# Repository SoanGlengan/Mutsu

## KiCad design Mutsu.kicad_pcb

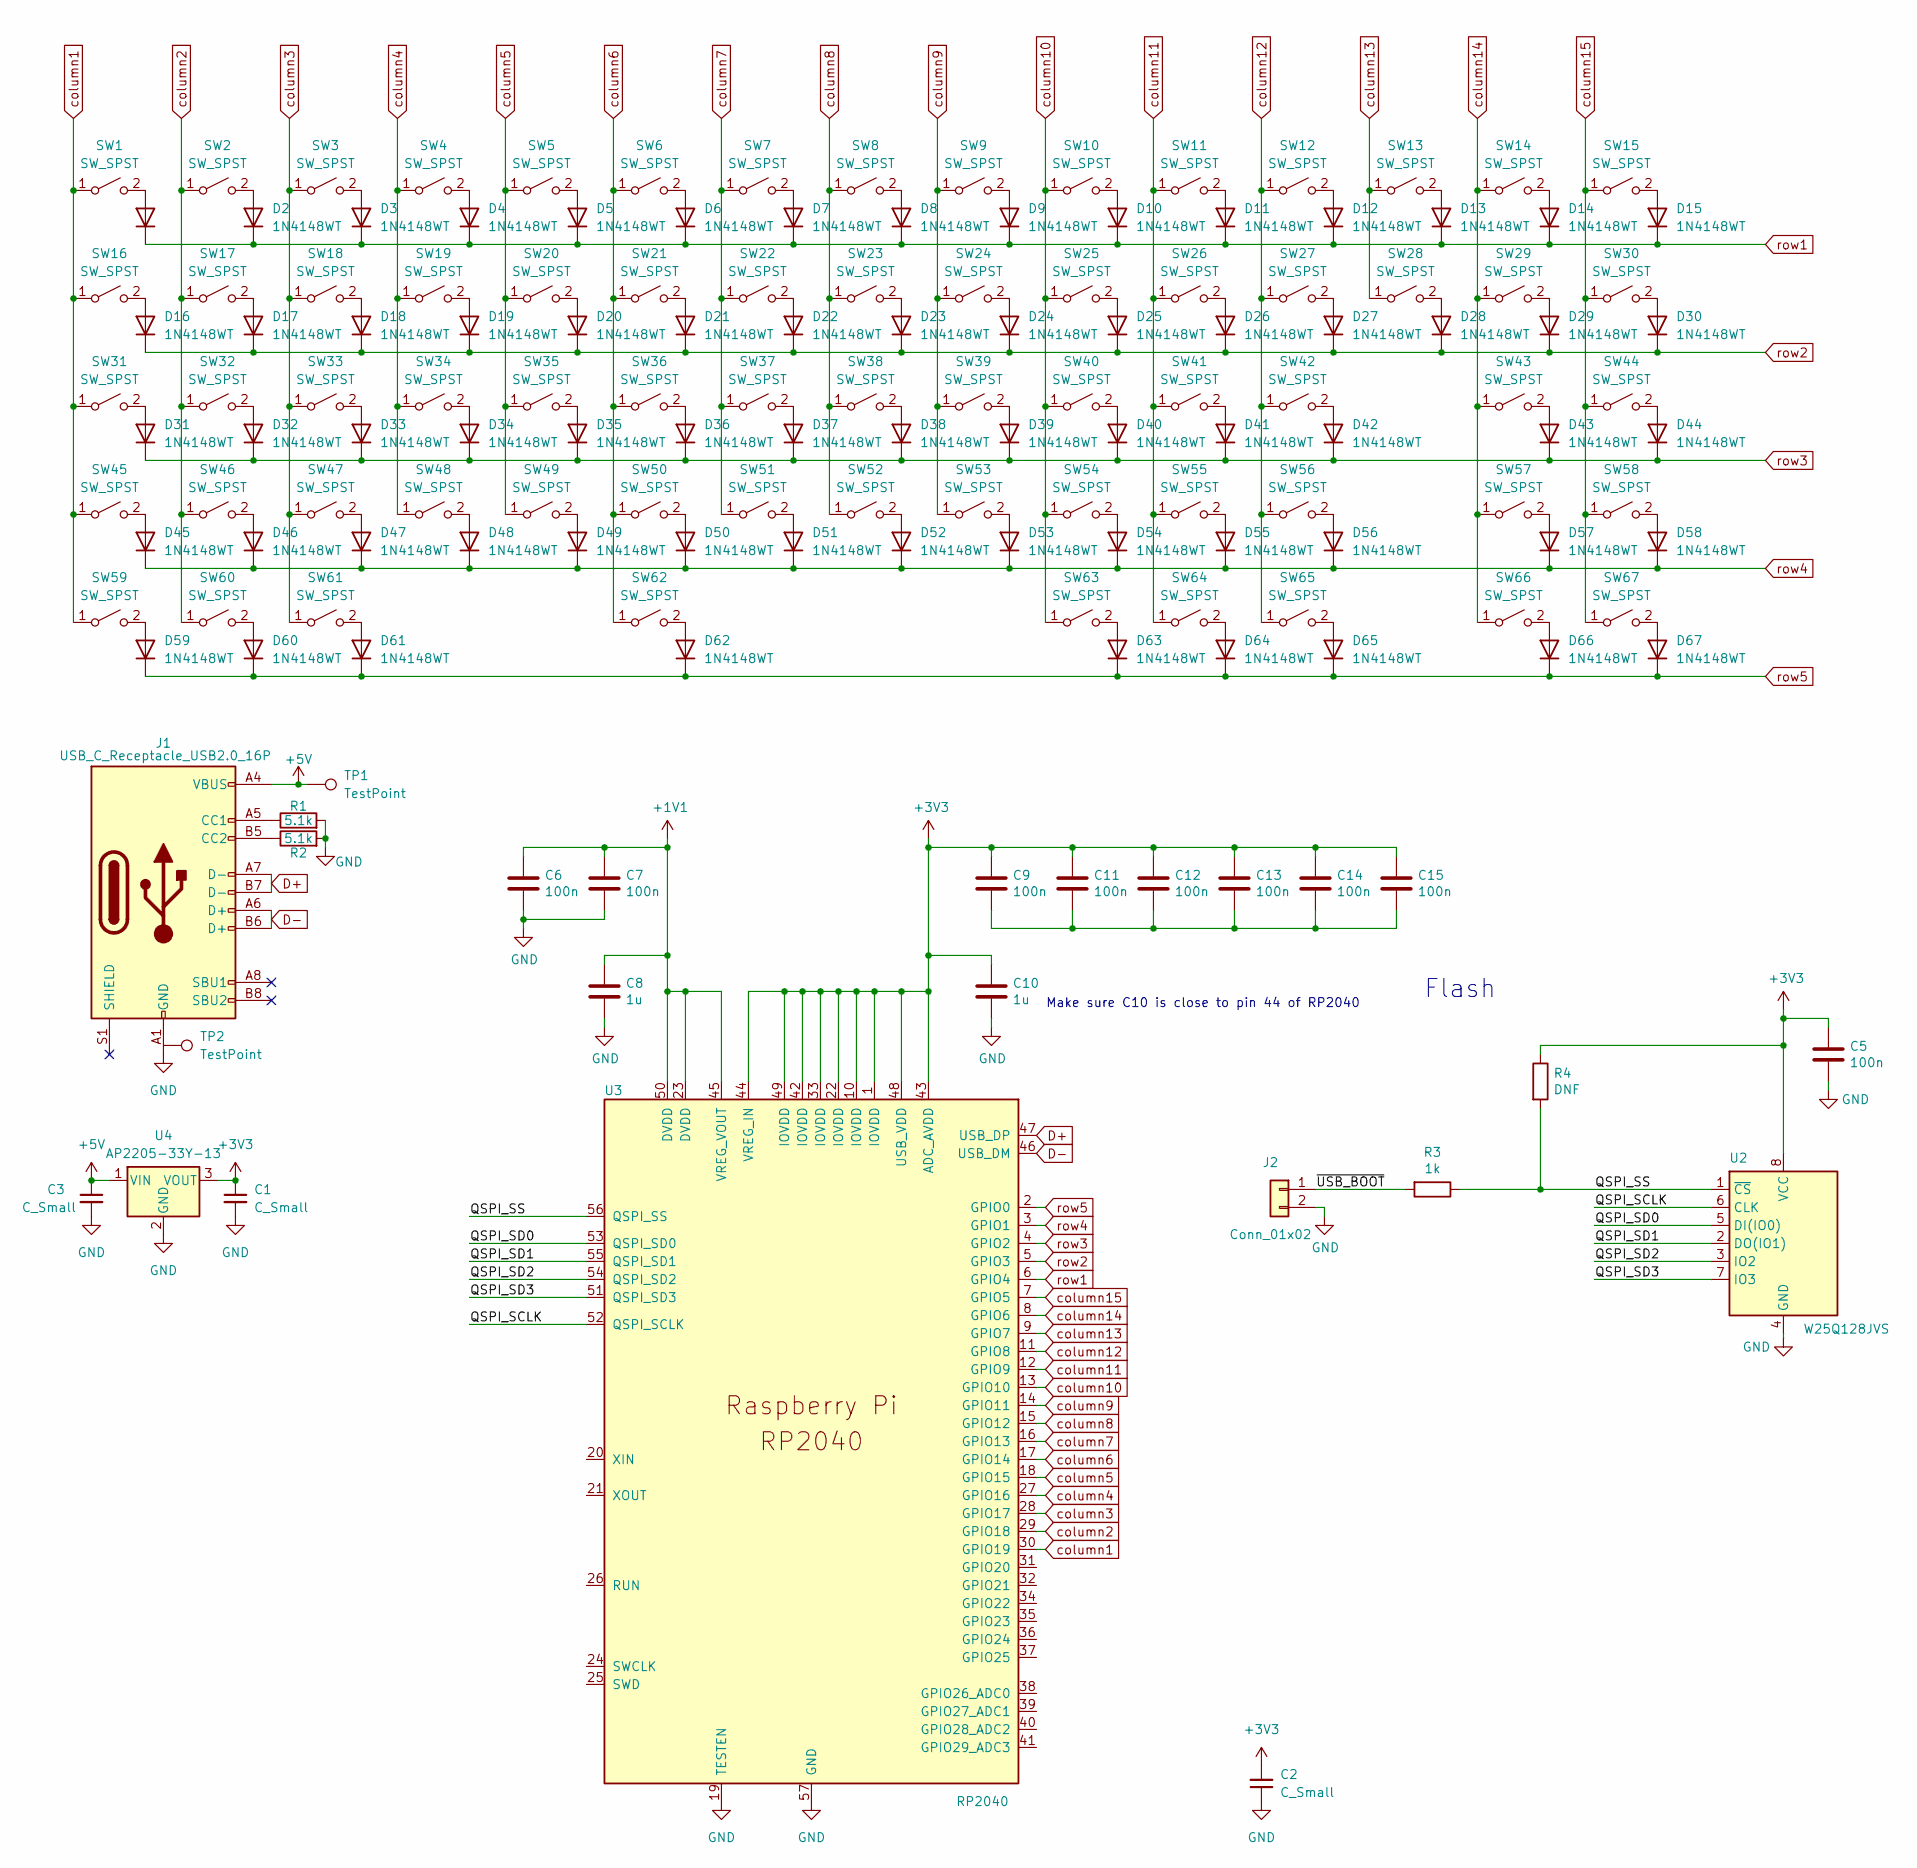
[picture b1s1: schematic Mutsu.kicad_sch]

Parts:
C1, C2, C3: C_Small
C5, C6, C7, C9, C11, C12, C13, C14, C15: 100n; C_0402_1005Metric
C8, C10: 1u; C_0402_1005Metric
D1: 1N4148wt; D_SOD-523
D2, D3, D4, D5, D6, D7, D8, D9, D10, D11, D12, D13, D14, D15, D16, D17, D18, D19, D20, D21, D22, D23, D24, D25, D26, D27, D28, D29, D30, D31, D32, D33, D34, D35, D36, D37, D38, D39, D40, D41, D42, D43, D44, D45, D46, D47, D48, D49, D50, D51, D52, D53, D54, D55, D56, D57, D58, D59, D60, D61, D62, D63, D64, D65, D66, D67: 1N4148WT; D_SOD-523
J1: USB_C_Receptacle_USB2.0_16P; USB_C_Receptacle_GCT_USB4105-xx-A_16P_TopMnt_Horizontal
J2: Conn_01x02; PinHeader_1x02_P2.54mm_Vertical
R1, R2: 5.1k
R3: 1k; R_0402_1005Metric
R4: DNF; R_0402_1005Metric
SW1, SW2, SW3, SW4, SW5, SW6, SW7, SW8, SW9, SW10, SW11, SW12, SW13, SW14, SW15, SW16, SW17, SW18, SW19, SW20, SW21, SW22, SW23, SW24, SW25, SW26, SW27, SW28, SW29, SW30, SW31, SW32, SW33, SW34, SW35, SW36, SW37, SW38, SW39, SW40, SW41, SW42, SW43, SW44, SW45, SW46, SW47, SW48, SW49, SW50, SW51, SW52, SW53, SW54, SW55, SW56, SW57, SW58, SW59, SW60, SW61, SW62, SW63, SW64, SW65, SW66, SW67: SW_SPST; Kailh_socket_PG1350
TP1, TP2: TestPoint
U2: W25Q128JVS; SOIC-8_5.23x5.23mm_P1.27mm
U3: RP2040; RP2040-QFN-56
U4: AP2205-33Y-13; SOT-89-3

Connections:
+1V1: C6.1, C7.1, C8.1, U3.23 (DVDD), U3.45 (VREG_VOUT), U3.50 (DVDD); also elsewhere on the board
+3V3: C1.1, C2.2, C5.1, C9.1, C10.1, C11.1, C12.1, C13.1, C14.1, C15.1, R4.1, U2.8 (VCC), U3.1 (IOVDD), U3.10 (IOVDD), U3.22 (IOVDD), U3.33 (IOVDD), U3.42 (IOVDD), U3.43 (ADC_AVDD), U3.44 (VREG_IN), U3.48 (USB_VDD), U3.49 (IOVDD), U4.3 (VOUT); also elsewhere on the board
+5V: C3.1, J1.A4 (VBUS), J1.A9 (VBUS), J1.B4 (VBUS), J1.B9 (VBUS), TP1.1, U4.1 (VIN)
/QSPI_SS: R3.1, R4.2, U2.1 (~CS), U3.56 (QSPI_SS)
/~USB_BOOT: J2.1, R3.2
D+: J1.A7 (D-), J1.B7 (D-), U3.47 (USB_DP); also elsewhere on the board
D-: J1.A6 (D+), J1.B6 (D+), U3.46 (USB_DM); also elsewhere on the board
GND: C1.2, C2.1, C3.2, C5.2, C6.2, C7.2, C8.2, C10.2, J1.A1 (GND), J1.A12 (GND), J1.B1 (GND), J1.B12 (GND), J2.2, R1.2, R2.2, U2.4 (GND), U3.19 (TESTEN), U3.57 (GND), U4.2 (GND); also elsewhere on the board
unnamed 10: C9.2, C11.2, C12.2, C13.2, C14.2, C15.2; also elsewhere on the board
unnamed: D1.2 (A), SW1.2 (B)
unnamed: D2.2 (A), SW2.2 (B)
unnamed: D3.2 (A), SW3.2 (B)
unnamed: D4.2 (A), SW4.2 (B)
unnamed: D5.2 (A), SW5.2 (B)
unnamed: D6.2 (A), SW6.2 (B)
unnamed: D7.2 (A), SW7.2 (B)
unnamed: D8.2 (A), SW8.2 (B)
unnamed: D9.2 (A), SW9.2 (B)
unnamed: D10.2 (A), SW10.2 (B)
unnamed: D11.2 (A), SW11.2 (B)
unnamed: D12.2 (A), SW12.2 (B)
unnamed: D13.2 (A), SW13.2 (B)
unnamed: D14.2 (A), SW14.2 (B)
unnamed: D15.2 (A), SW15.2 (B)
unnamed: D16.2 (A), SW16.2 (B)
unnamed: D17.2 (A), SW17.2 (B)
unnamed: D18.2 (A), SW18.2 (B)
unnamed: D19.2 (A), SW19.2 (B)
unnamed: D20.2 (A), SW20.2 (B)
unnamed: D21.2 (A), SW21.2 (B)
unnamed: D22.2 (A), SW22.2 (B)
unnamed: D23.2 (A), SW23.2 (B)
unnamed: D24.2 (A), SW24.2 (B)
unnamed: D25.2 (A), SW25.2 (B)
unnamed: D26.2 (A), SW26.2 (B)
unnamed: D27.2 (A), SW27.2 (B)
unnamed: D28.2 (A), SW28.2 (B)
unnamed: D29.2 (A), SW29.2 (B)
unnamed: D30.2 (A), SW30.2 (B)
unnamed: D31.2 (A), SW31.2 (B)
unnamed: D32.2 (A), SW32.2 (B)
unnamed: D33.2 (A), SW33.2 (B)
unnamed: D34.2 (A), SW34.2 (B)
unnamed: D35.2 (A), SW35.2 (B)
unnamed: D36.2 (A), SW36.2 (B)
unnamed: D37.2 (A), SW37.2 (B)
unnamed: D38.2 (A), SW38.2 (B)
unnamed: D39.2 (A), SW39.2 (B)
unnamed: D40.2 (A), SW40.2 (B)
unnamed: D41.2 (A), SW41.2 (B)
unnamed: D42.2 (A), SW42.2 (B)
unnamed: D43.2 (A), SW43.2 (B)
unnamed: D44.2 (A), SW44.2 (B)
unnamed: D45.2 (A), SW45.2 (B)
unnamed: D46.2 (A), SW46.2 (B)
unnamed: D47.2 (A), SW47.2 (B)
unnamed: D48.2 (A), SW48.2 (B)
unnamed: D49.2 (A), SW49.2 (B)
unnamed: D50.2 (A), SW50.2 (B)
unnamed: D51.2 (A), SW51.2 (B)
unnamed: D52.2 (A), SW52.2 (B)
unnamed: D53.2 (A), SW53.2 (B)
unnamed: D54.2 (A), SW54.2 (B)
unnamed: D55.2 (A), SW55.2 (B)
unnamed: D56.2 (A), SW56.2 (B)
unnamed: D57.2 (A), SW57.2 (B)
unnamed: D58.2 (A), SW58.2 (B)
unnamed: D59.2 (A), SW59.2 (B)
unnamed: D60.2 (A), SW60.2 (B)
unnamed: D61.2 (A), SW61.2 (B)
unnamed: D62.2 (A), SW62.2 (B)
unnamed: D63.2 (A), SW63.2 (B)
unnamed: D64.2 (A), SW64.2 (B)
unnamed: D65.2 (A), SW65.2 (B)
unnamed: D66.2 (A), SW66.2 (B)
unnamed: D67.2 (A), SW67.2 (B)
unnamed: J1.A5 (CC1), R1.1
unnamed: J1.B5 (CC2), R2.1
unnamed: U2.2 (DO(IO1)), U3.55 (QSPI_SD1)
unnamed: U2.3 (IO2), U3.54 (QSPI_SD2)
unnamed: U2.5 (DI(IO0)), U3.53 (QSPI_SD0)
unnamed: U2.6 (CLK), U3.52 (QSPI_SCLK)
unnamed: U2.7 (IO3), U3.51 (QSPI_SD3)
column1: SW1.1 (A), SW16.1 (A), SW31.1 (A), SW45.1 (A), SW59.1 (A), U3.30 (GPIO19); also elsewhere on the board
column2: SW2.1 (A), SW17.1 (A), SW32.1 (A), SW46.1 (A), SW60.1 (A), U3.29 (GPIO18); also elsewhere on the board
column3: SW3.1 (A), SW18.1 (A), SW33.1 (A), SW47.1 (A), SW61.1 (A), U3.28 (GPIO17); also elsewhere on the board
column4: SW4.1 (A), SW19.1 (A), SW34.1 (A), SW48.1 (A), U3.27 (GPIO16); also elsewhere on the board
column5: SW5.1 (A), SW20.1 (A), SW35.1 (A), SW49.1 (A), U3.18 (GPIO15); also elsewhere on the board
column6: SW6.1 (A), SW21.1 (A), SW36.1 (A), SW50.1 (A), SW62.1 (A), U3.17 (GPIO14); also elsewhere on the board
column7: SW7.1 (A), SW22.1 (A), SW37.1 (A), SW51.1 (A), U3.16 (GPIO13); also elsewhere on the board
column8: SW8.1 (A), SW23.1 (A), SW38.1 (A), SW52.1 (A), U3.15 (GPIO12); also elsewhere on the board
column9: SW9.1 (A), SW24.1 (A), SW39.1 (A), SW53.1 (A), U3.14 (GPIO11); also elsewhere on the board
column10: SW10.1 (A), SW25.1 (A), SW40.1 (A), SW54.1 (A), SW63.1 (A), U3.13 (GPIO10); also elsewhere on the board
column11: SW11.1 (A), SW26.1 (A), SW41.1 (A), SW55.1 (A), SW64.1 (A), U3.12 (GPIO9); also elsewhere on the board
column12: SW12.1 (A), SW27.1 (A), SW42.1 (A), SW56.1 (A), SW65.1 (A), U3.11 (GPIO8); also elsewhere on the board
column13: SW13.1 (A), SW28.1 (A), U3.9 (GPIO7); also elsewhere on the board
column14: SW14.1 (A), SW29.1 (A), SW43.1 (A), SW57.1 (A), SW66.1 (A), U3.8 (GPIO6); also elsewhere on the board
column15: SW15.1 (A), SW30.1 (A), SW44.1 (A), SW58.1 (A), SW67.1 (A), U3.7 (GPIO5); also elsewhere on the board
row1: D1.1 (K), D2.1 (K), D3.1 (K), D4.1 (K), D5.1 (K), D6.1 (K), D7.1 (K), D8.1 (K), D9.1 (K), D10.1 (K), D11.1 (K), D12.1 (K), D13.1 (K), D14.1 (K), D15.1 (K), U3.6 (GPIO4); also elsewhere on the board
row2: D16.1 (K), D17.1 (K), D18.1 (K), D19.1 (K), D20.1 (K), D21.1 (K), D22.1 (K), D23.1 (K), D24.1 (K), D25.1 (K), D26.1 (K), D27.1 (K), D28.1 (K), D29.1 (K), D30.1 (K), U3.5 (GPIO3); also elsewhere on the board
row3: D31.1 (K), D32.1 (K), D33.1 (K), D34.1 (K), D35.1 (K), D36.1 (K), D37.1 (K), D38.1 (K), D39.1 (K), D40.1 (K), D41.1 (K), D42.1 (K), D43.1 (K), D44.1 (K), U3.4 (GPIO2); also elsewhere on the board
row4: D45.1 (K), D46.1 (K), D47.1 (K), D48.1 (K), D49.1 (K), D50.1 (K), D51.1 (K), D52.1 (K), D53.1 (K), D54.1 (K), D55.1 (K), D56.1 (K), D57.1 (K), D58.1 (K), U3.3 (GPIO1); also elsewhere on the board
row5: D59.1 (K), D60.1 (K), D61.1 (K), D62.1 (K), D63.1 (K), D64.1 (K), D65.1 (K), D66.1 (K), D67.1 (K), U3.2 (GPIO0); also elsewhere on the board

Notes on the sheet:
Flash
Make sure C10 is close to pin 44 of RP2040

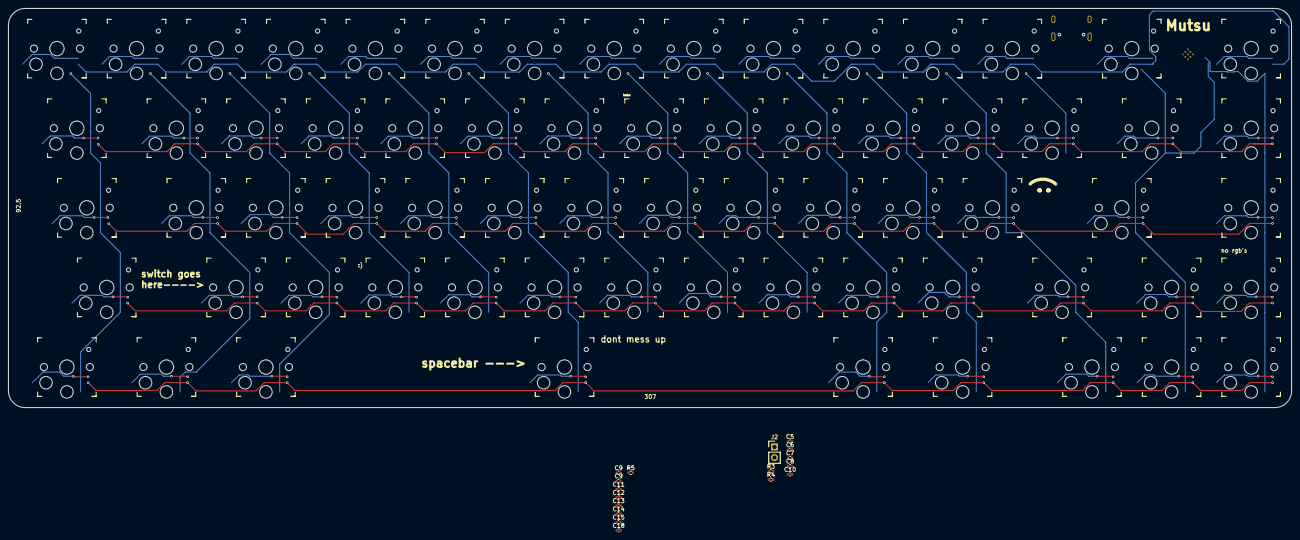
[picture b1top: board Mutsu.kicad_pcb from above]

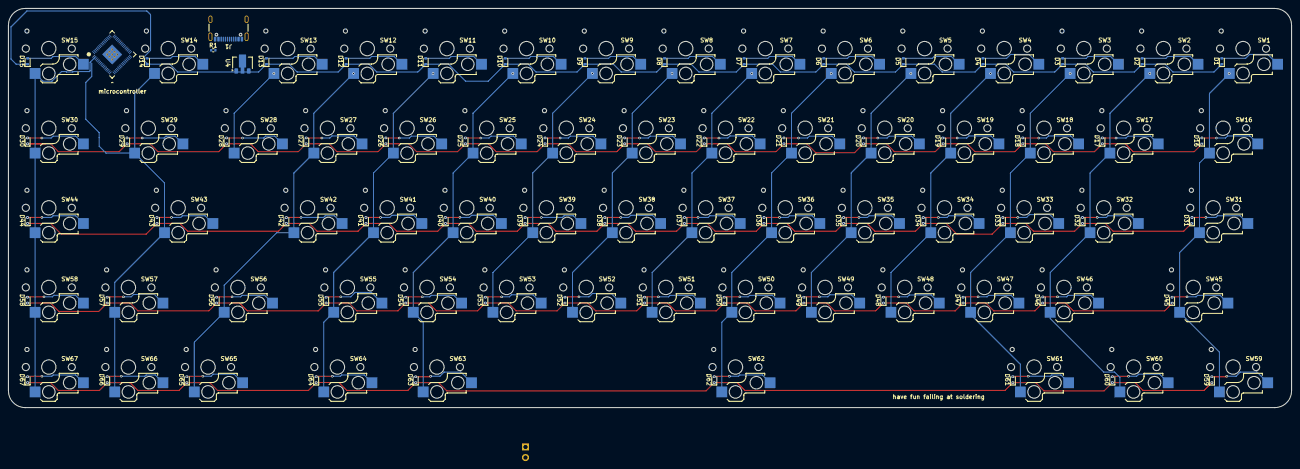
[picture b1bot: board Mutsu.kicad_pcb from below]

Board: 2 copper layers, 307.0 x 95.5 mm, 155 parts (71 on the bottom side), 98 nets.

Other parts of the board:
C9#2, C18: 100n; C_0402_1005Metric
R5: 33; R_0402_1005Metric
U1: RP2350A-QFN60; RP2350A_QFN-60_EP_7.75x7.75_Pitch0.4mm

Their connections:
+1V1: U1.50 (VREG_FB); also elsewhere on the board
+3V3: C9#2.1, C18.1, R5.1, U1.1 (IOVDD), U1.11 (IOVDD), U1.20 (IOVDD), U1.30 (IOVDD), U1.38 (IOVDD), U1.44 (ADC_AVDD), U1.45 (IOVDD), U1.49 (VREG_VIN), U1.53 (USB_OTP_VDD), U1.54 (QSPI_IOVDD); also elsewhere on the board
/VREG_AVDD: R5.2, U1.46 (VREG_AVDD)
D+: U1.52 (USB_DP); also elsewhere on the board
D-: U1.51 (USB_DM); also elsewhere on the board
GND: C18.2, U1.47 (VREG_PGND), U1.61 (GND); also elsewhere on the board
unnamed 10: C9#2.2; also elsewhere on the board
column1: U1.17 (GPIO13); also elsewhere on the board
column2: U1.16 (GPIO12); also elsewhere on the board
column3: U1.15 (GPIO11); also elsewhere on the board
column4: U1.14 (GPIO10); also elsewhere on the board
column5: U1.13 (GPIO9); also elsewhere on the board
column6: U1.12 (GPIO8); also elsewhere on the board
column7: U1.10 (GPIO7); also elsewhere on the board
column8: U1.9 (GPIO6); also elsewhere on the board
column9: U1.8 (GPIO5); also elsewhere on the board
column10: U1.7 (GPIO4); also elsewhere on the board
column11: U1.5 (GPIO3); also elsewhere on the board
column12: U1.4 (GPIO2); also elsewhere on the board
column13: U1.3 (GPIO1); also elsewhere on the board
column14: U1.29 (GPIO18); also elsewhere on the board
column15: U1.2 (GPIO0); also elsewhere on the board
row1: U1.31 (GPIO19); also elsewhere on the board
row2: U1.18 (GPIO14); also elsewhere on the board
row3: U1.19 (GPIO15); also elsewhere on the board
row4: U1.27 (GPIO16); also elsewhere on the board
row5: U1.28 (GPIO17); also elsewhere on the board

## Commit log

2025-08-16 second commit
2025-08-16 third commit
2025-08-21 fourth commit
2026-01-09 hehe
